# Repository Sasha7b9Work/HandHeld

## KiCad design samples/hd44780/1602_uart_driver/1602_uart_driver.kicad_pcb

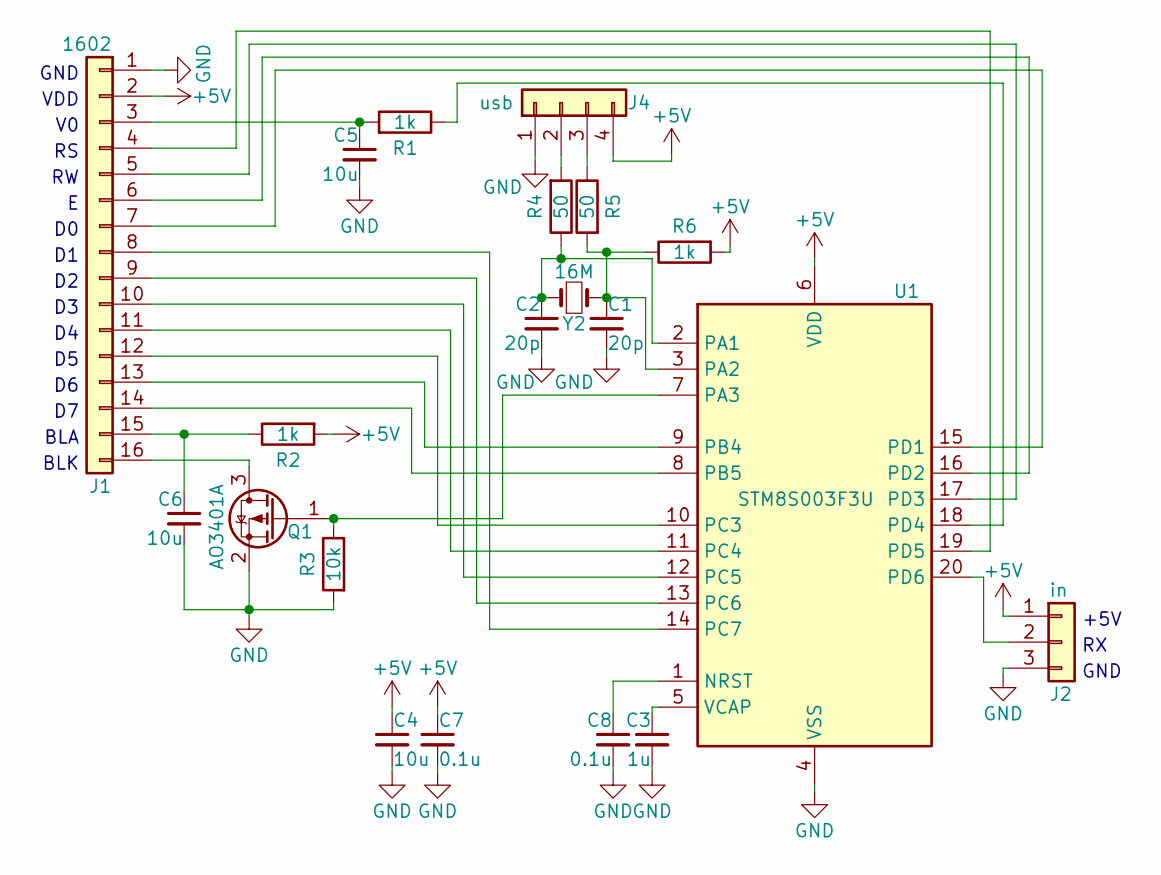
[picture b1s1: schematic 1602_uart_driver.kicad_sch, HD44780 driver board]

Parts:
C1, C2: 20p; C_0402_1005Metric
C3: 1u; C_0805_2012Metric
C4, C5, C6: 10u; C_0805_2012Metric
C7, C8: 0.1u; C_0402_1005Metric
J1: 1602; PinHeader_1x16_P2.54mm_Vertical
J2: in; PinHeader_1x03_P2.54mm_Vertical
J4: usb; PinSocket_1x04_P2.54mm_Vertical
Q1: AO3401A; SOT-23
R1, R2, R6: 1k; R_0402_1005Metric
R3: 10k; R_0402_1005Metric
R4, R5: 50; R_0402_1005Metric
U1: STM8S003F3U; ST_UFQFPN-20_3x3mm_P0.5mm
Y2: 16M; Crystal_SMD_5032-2Pin_5.0x3.2mm

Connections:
+5V: C4.1, C7.1, J1.2, J2.1, J4.4, R2.2, R6.2, U1.6 (VDD)
GND: C1.2, C2.2, C3.2, C4.2, C5.2, C6.2, C7.2, C8.2, J1.1, J2.3, J4.1, Q1.2 (S), R3.2, U1.4 (VSS)
unnamed: C5.1, J1.3, R1.2
unnamed: J1.4, U1.19 (PD5)
unnamed: J1.5, U1.17 (PD3)
unnamed: J1.6, U1.16 (PD2)
unnamed: J1.7, U1.15 (PD1)
unnamed: J1.8, U1.14 (PC7)
unnamed: J1.9, U1.13 (PC6)
unnamed: J1.10, U1.12 (PC5)
unnamed: J1.11, U1.11 (PC4)
unnamed: J1.12, U1.10 (PC3)
unnamed: J1.13, U1.9 (PB4)
unnamed: J1.14, U1.8 (PB5)
unnamed: C6.1, J1.15, R2.1
unnamed: J1.16, Q1.3 (D)
unnamed: J2.2, U1.20 (PD6)
unnamed: J4.2, R4.2
unnamed: J4.3, R5.1
unnamed: Q1.1 (G), R3.1, U1.7 (PA3)
unnamed: C8.1, U1.1 (NRST)
unnamed: C2.1, R4.1, U1.2 (PA1), Y2.1
unnamed: C1.1, R5.2, R6.1, U1.3 (PA2), Y2.2
unnamed: R1.1, U1.18 (PD4)
unnamed: C3.1, U1.5 (VCAP)

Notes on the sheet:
BLA
+5V
GND
VDD
BLK

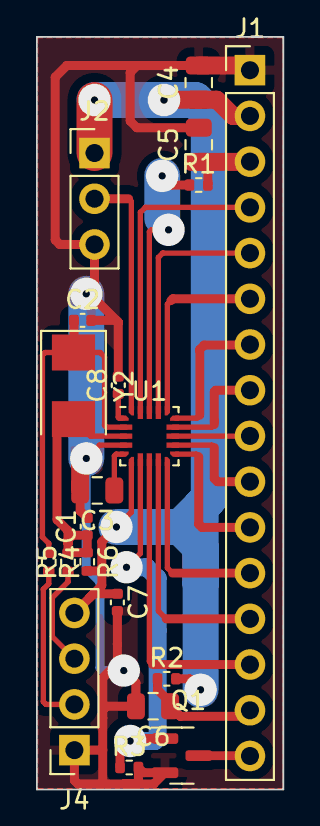
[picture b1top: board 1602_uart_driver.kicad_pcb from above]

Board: 2 copper layers, 13.7 x 41.8 mm, 20 parts (0 on the bottom side), 25 nets.

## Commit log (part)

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2024-04-17 Приделан вход в глубокий сон
2024-04-18 DeviceEnergy потребляет 327 mkA
2024-04-18 detrash
2024-04-18 Клавиатура перекинута на прерывания
2024-04-18 Выкинут таймер на приёмник
2024-04-18 Приём битов приёмника по тактам
2024-04-18 вёрнут обратно приёмник
2024-04-18 На PB15 теперь длительность расчёта бита
2024-04-18 Частота 26 МГц
2024-04-18 Частота 13 МГц
2024-04-18 Частота 6.5 МГц
2024-04-18 Частота 3.25 МГц
2024-04-18 Контрольная сумма для дисплея
2024-04-18 Готовимся к переключению частот
2024-04-18 По включении в режиме сна. По нажатию кнопки переходит в рабочий
2024-04-18 Сделано выключение дисплея
2024-04-18 В начале каждого цикла спим
2024-04-18 Вне приёма клоков от приёмника устройство должно спать
2024-04-18 Запускаем таймер по началу клоков
2024-04-19 Теперь не будет засыпать во время приёма
2024-04-19 Дисплей заработает на следующем вызове
2024-04-19 52 МГц на дисплей
2024-04-19 Образцовая версяи
2024-04-19 Первая версия цветомузыки
2024-04-19 Первая версия светомузыки
2024-04-19 Вибратор тоже подключён
2024-04-19 Забиты коды
2024-04-20 Цвета коррекция
2024-04-20 Выбор цвета отображается своим цветом
2024-04-20 Вызов цветом
2024-04-20 X приводит к гашению экрана
2024-04-22 Исправлен I2C на программную версию
2024-04-23 Заготовка для 1602
2024-04-23 Готов проект для 1602Э
2024-04-23 Рыба для 1602 готова
2024-04-23 компилируется 1602
2024-04-24 refact
2024-04-24 Первая мелодия сделана на
2024-04-24 warnings PVS-Studio
2024-04-25 Поправлен баг PCF8563 при записи в контрольный регистр
2024-04-25 Теперь будильник должен срабатывать
2024-04-25 Работает GUI-версия
2024-04-25 Добавлена функция на переключение Choice
2024-04-25 Сделано будильник вкл/откл
2024-04-25 Будильник устанавливается после изменения времени только если он включён
2024-04-25 Индикация будильника
2024-04-25 Отключение будильника, отключена проверка контрольной суммы на выводе дисплея
2024-04-25 Удалены исследовательские проекты
2024-04-27 Изменена громкость
2024-04-29 Возможно, будильник будет включать устройство
2024-04-29 Добавлены сирены для 9-й и 10-й мелодий
2024-04-30 1602 оставлен только дисплей
2024-04-30 Работает текстовый вывод на дисплей
2024-04-30 ускорение
2024-05-02 Не работает приём с дальномера
2024-05-02 Подписаны мелодии
2024-05-03 Исправлено зацикливание
2024-05-03 Может, сейчас звук не зациклен
2024-05-03 Warnings
2024-05-03 vs_win Время теперь берётся из системных часов
2024-05-07 Недоделанное хранилище в ПЗУ
2024-05-07 Теоретически работает хранилище в RAM@
2024-05-07 Убрали индикацию заряда
2024-05-08 Пробуем считывать время будильника из микросхемы
2024-05-08 v002
2024-05-08 v003
2024-05-08 v004
2024-05-12 v005 исправлен баг в будильнике.
2024-05-13 работает вывод на дисплей
2024-05-13 Обе строки
2024-05-13 Не должно мерцать
2024-05-13 Вёрнута работоспособность клавиатуры на 7735
2024-05-13 На 1602 должна работать клавиатура
2024-05-13 Заготовлено для двух типов дисплеев
2024-05-13 Таблица преобразования русских символов в английские
2024-05-13 Время должно рисоваться
2024-05-13 Меню частично должно рисоваться
2024-05-13 компилируется win-версия
2024-05-13 отрисовываются все элементы меню
2024-05-13 Вывод на дисплей 1602 закончен
2024-05-13 Подготовка к загрузке символов в CGRAM
2024-05-13 Забиты первые буквы
2024-05-13 Почти готово к загрузке символов в CGARAM
2024-05-13 Осталось написать функцию записи символов в CGRAM
2024-05-14 исправлена настройка времени и даты
2024-05-14 Выбор даты инвертированными символами
2024-05-14 Убраны цифровые символы
2024-05-14 Эксперимент с миганием
2024-05-15 Tеперь возможных цветов вызова - 7 штук, по количеству цветов в светодиоде 1602
2024-05-15 Заготовка для драйвера цветного светодиода. Осталось только переключать соотвествующие пины
2024-05-15 Должны работать цветные светодиоды в 1602
2024-05-16 Оптимизирован вывод на дисплей 1602
2024-05-16 Дисплей, по идее, должен отключаться
2024-05-16 Пробуем полностью потушить дисплей
2024-05-17 релизная версия работает 1602
2024-05-21 По будильнику должен включаться экран
2024-05-21 Мучаю клавиатуру
2024-05-21 Время будильника увелчиено до 1 минуты
2024-05-21 Клавиатура
2024-05-23 Индикатор заряда
2024-05-27 У подправлена
2024-05-27 Пробуем убрлать вибратор в 1602
2024-05-27 Теперь вибро идёт на PA2
2024-11-21 Новый проект для спящего режима
2024-12-05 Настройки отладчика
2024-12-05 Начинаем исследования
2025-02-24 Добавлена новая документация
2025-02-25 Добавлен SDK
2025-11-07 wxWidgets 3.3.1
2025-12-14 исправлены скрипты сборки под Visual Studio 2026
